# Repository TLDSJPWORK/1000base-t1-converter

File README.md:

# 1000base-t1-converter for Education

学習用 1000BASE-T1 Media Converter

## 特徴

- Texas Instruments社のDP83TG720とDP83867を使用した、1000BASE-T1 ↔ 1000BASE-T（RJ45）のメディアコンバーターです。
- RP2040を搭載し、USB接続で各PHY ICの状態確認とレジスタ設定ができます。MDIOを通してPHY層の動きを学習できます。
- 基板上のスイッチで1000BASE-T1のmaster／slaveを選択できます。
- Ethernetフレームは2個のPHY間をRGMIIで転送し、RP2040はPHYの設定・状態確認を担当します。
- KiCadの回路図・PCB、製造データ、ケースのSTL・STEPを公開しています。

## 基板

収録している回路・基板はRev1.0です。基板外形は125 × 70 mmです。
基板イメージは参考であり、改良により実物と異なる場合があります。

## 基板の設定と説明

| 図の番号 | 接続部 | 使い方 |
| --- | --- | --- |
| 1 | USB Type-C（USB601） | 5 V給電、USB診断、ファームウェア更新に使用します。 |
| 2 | Boot（SW601） | ファームウェア書込み時のBOOTSELボタンです。 |
| 3 | Reset（SW602） | RP2040と両PHY（DP83TG720・DP83867）をリセットします。master／slave変更後は全電源を再投入してください。 |
| 4 | Sleep / WAKE（U205） | 通常の通信ではWAKEをHighに設定します。接点状態は下表を参照してください。 |
| 5 | T1（CN201） | 1000BASE-T1を接続します。pin 1=T1_P、pin 2=T1_Nです。 |
| 6 | Master/Slave（U203） | 対向機器と、一方をmaster、もう一方をslaveに設定します。 |
| 7 | RJ45（RJ501） | 1000BASE-T対応機器を接続します。 |

### スイッチの接点設定

U203・U205はそれぞれ2回路のスイッチです。ONは接続、OFFは開放を示します。
図中の3Dモデルのレバー位置は設定例ではありません。スイッチ本体のON表示と端子番号を確認してください。

| スイッチ | 設定 | 1–4の接点 | 2–3の接点 |
| --- | --- | --- | --- |
| Master/Slave（U203） | **master** | **ON** | **OFF** |
| Master/Slave（U203） | **slave** | **OFF** | **ON** |
| Sleep / WAKE（U205） | **通常動作（WAKE=High）** | **ON** | **OFF** |
| Sleep / WAKE（U205） | Sleep要求（WAKE=Low） | **OFF** | **ON** |

**両回路を同時にONにしないでください。** 上表の組合せで、一方をON、もう一方をOFFにしてください。
Sleepへの移行はPHYの設定やリンク状態にも依存します。
設定変更は全電源を外して行い、変更後は基板の全電源を再投入してください。
詳しい接続手順と給電方法は[取扱説明書](docs/user-manual.md)を参照してください。

### LEDの説明

上の「基板の設定と説明」図の青い番号8〜14が、下表に対応します。14はRJ45内蔵の2個のLEDをまとめて示しています。

Power・Reset・RP_GPIO25は、基板手前のシルク表示で識別できます。
T1側にはSleepスイッチ付近のU202と、Master/Slaveスイッチ付近のU201・U204があります。

| 図の番号 | 表示・位置 | 部品 | 説明 |
| --- | --- | --- | --- |
| 8 | Power | D402（緑） | 基板の5 V電源に接続された給電表示です。 |
| 9 | Reset | LED602（赤） | RP2040と両PHY（DP83TG720・DP83867）の共通リセット表示です。共通リセット信号がLowの間に点灯し、Resetボタン操作時にも点灯します。 |
| 10 | RP_GPIO25 | LED601（緑） | RP2040のGPIO25で制御するLEDです。点灯・点滅の意味はファームウェアに依存します。 |
| 11 | T1側・Sleepスイッチ付近 | U202（緑） | DP83TG720のLED_1出力に接続しています。リンク成立で点灯し、送受信時に点滅します。 |
| 12 | T1側・Master/Slaveスイッチ付近 | U201（緑） | **Master設定時のリンク表示**です。DP83TG720のLED_0出力を表示します。 |
| 13 | T1側・Master/Slaveスイッチ付近 | U204（緑） | **Slave設定時のリンク表示**です。DP83TG720のLED_0出力を表示します。 |
| 14 | RJ45内蔵LED | RJ501・LED_0側 | DP83867のリンク表示です。 |
| 14 | RJ45内蔵LED | RJ501・LED_2側 | DP83867の送受信アクティビティ表示です。 |

PHY関連のLED表示は、レジスタ設定によって変更できます。
LED出力の仕様はTIの[DP83TG720R-Q1データシート（IO_MUX_CFG_1）](https://www.ti.com/lit/ds/symlink/dp83tg720r-q1.pdf)と
[DP83867IR/CRデータシート（LED Interface）](https://www.ti.com/lit/ds/symlink/dp83867ir.pdf)を参照してください。

## 使用例

### メディアコンバーターとして使う

RP2040に[専用ファームウェア](https://github.com/TLDSJPWORK/1000base-t1-converter-soft)を書き込み、
T1側のmaster／slaveを設定して、1000BASE-T1機器とRJ45側の1000BASE-T機器を接続します。
ファームウェアが起動時にPHYの通信設定を適用します。

2台を `Mac ↔ converter ↔ converter ↔ Raspberry Pi` と接続し、
1000BASE-T full-duplex、両T1 PHYのリンク、ARP、20回のping（損失0%）、SSHポート到達を確認しています。
詳しい試験条件と確認範囲は[検証記録](https://github.com/TLDSJPWORK/1000base-t1-converter-soft/blob/main/docs/validation.md)を参照してください。

### PHYの動きを確認する

USB CDCシリアルから、PHYの検出、リンク状態の確認、レジスタの読み書きができます。
コマンドと使用方法は[取扱説明書のUSB診断](docs/user-manual.md#4-usb診断)と
[ファームウェアのREADME](https://github.com/TLDSJPWORK/1000base-t1-converter-soft)を参照してください。

## ケースと完成品の構成

[PLAケース](case/)の設計外形は132.8 × 77.8 × 28.0 mmです。上下ケースのSTL・STEPを収録しています。

ケース組立例。手前にT1端子、設定スイッチ、RJ45端子が並びます。

ケース入り完成品には、MATEnetアダプタ（ツイストペア線接続・ケース付き）が付属します。アダプタの[基板設計・製造・ケースデータ](adapter/)も収録しています。

付属MATEnetアダプタの外観。本体側プラグの取付前の状態です。

## 製造データ

[Rev1.0の製造データ](production/)には、基板製作に使用したGerber ZIP・BOM・実装位置データを収録しています。
対応するKiCadソースは[hardware/](hardware/)に収録しています。

再製造する場合は、部品指定や未実装部品についての[Rev1.0の既知事項](docs/rev1.0-known-issues.md)を確認してください。

## 資料

- [取扱説明書](docs/user-manual.md)
- [回路図（PDF）](docs/1000base-t1-converter_schematic.pdf)
- [KiCad回路図・PCB](hardware/)
- [Gerber・BOM・実装位置](production/)
- [ケースのSTL・STEP](case/)
- [RP2040ファームウェア・レジスタ読み書きソフト](https://github.com/TLDSJPWORK/1000base-t1-converter-soft)
- [学習用100BASE-T1メディアコンバーター](https://github.com/TLDSJPWORK/100base-t1-converter)

## 販売・問い合わせ

スイッチサイエンス様での委託販売を予定しています。

- 販売ページ：【発売後掲載】
- 技術問い合わせ先：tldsjpwork@gmail.com

## 関連プロジェクト

- [100base-t1-converter](https://github.com/TLDSJPWORK/100base-t1-converter)：100 Mbpsの100BASE-T1に対応した学習用メディアコンバーターです。
- [1000base-t1-converter-soft](https://github.com/TLDSJPWORK/1000base-t1-converter-soft)：本基板のRP2040用ファームウェアです。PHYの初期設定、状態確認、レジスタの読み書きに使用します。

## ライセンス

ハードウェア設計、製造データ、文書、画像は[Creative Commons Attribution 4.0 International](LICENSE)で公開します。

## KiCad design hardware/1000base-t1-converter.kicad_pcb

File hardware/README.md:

# Hardware

KiCad 9で作成した1000BASE-T1コンバーター本体の設計データです。

`1000base-t1-converter.kicad_pro`を開いてください。回路図は次の階層シートに分かれています。

- `DP83867.kicad_sch`: 1000BASE-T PHY
- `DP83TG720.kicad_sch`: 1000BASE-T1 PHY
- `RJ45.kicad_sch`: RJ45インターフェース
- `RP2040.kicad_sch`: PHY管理マイコン
- `Power.kicad_sch`: 電源回路

製造データは[production/](../production/)にあります。

フットプリントと回路記号はKiCadファイルへ保存されています。3Dモデルの一部は
EasyEDA2KiCadのライブラリを参照するため、完全な3D表示にはKiCadで`EASYEDA2KICAD`
パス変数を設定してください。回路図・PCB編集と製造出力の確認には必須ではありません。

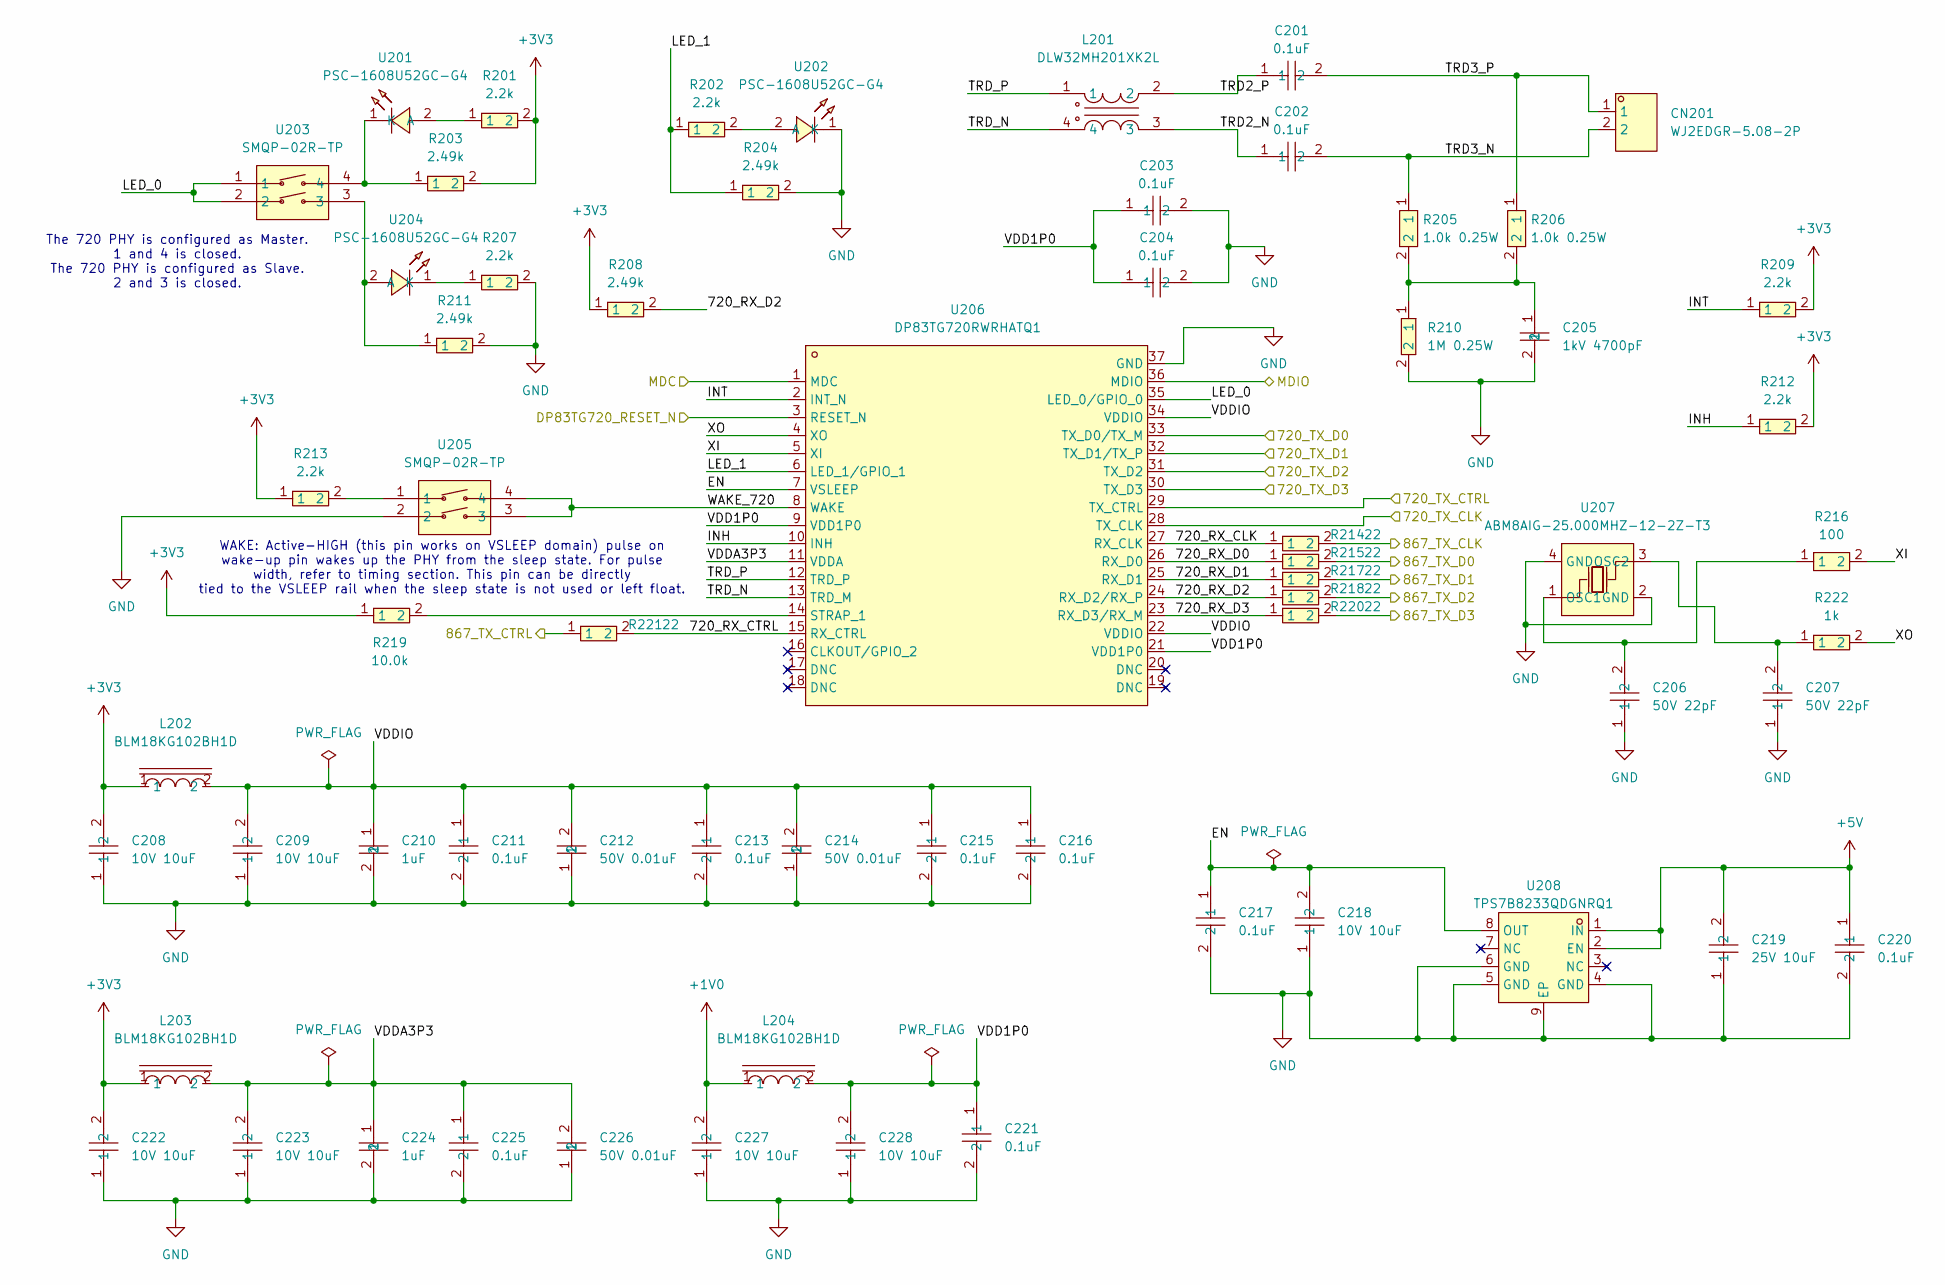
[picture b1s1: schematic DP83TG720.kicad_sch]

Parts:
C201, C202, C203, C204, C211, C213, C215, C216, C217, C220, C221, C225: 0.1uF; C0603; LCSC Part C14663
C205: 1kV 4700pF; C1206; LCSC Part C9192
C206, C207: 50V 22pF; C0603; LCSC Part C326840
C208, C209, C218, C222, C223, C227, C228: 10V 10uF; C0603; MPN GRM188Z71A106MA73D; LCSC Part C237435
C210, C224: 1uF; C0603; LCSC Part C15849
C212, C214, C226: 50V 0.01uF; C0603; LCSC Part C57112
C219: 25V 10uF; C0603; LCSC Part C96446
CN201: WJ2EDGR-5.08-2P; CONN-TH_WJ2EDGR-5.08-2P; MPN WJ2EDGR-5.08-02P-14-00A; LCSC Part C8383
L201: DLW32MH201XK2L; FILTER-SMD_4P-L3.2-W2.5-BL_DLW32SH510XK2L; MPN DLW32MH201XK2L; LCSC Part C883600
L202, L203, L204: BLM18KG102BH1D; L0603; MPN BLM18KG102BH1D; LCSC Part C560058
R201, R202, R207, R209, R212, R213: 2.2k; R0603; LCSC Part C4190
R203, R204, R208, R211: 2.49k; R0603; LCSC Part C22908
R205, R206: 1.0k 0.25W; R0603; LCSC Part C2653986
R210: 1M 0.25W; R1206; LCSC Part C108083
R214, R215, R217, R218, R220, R221: 22; R0603; LCSC Part C108405
R216: 100; R0603; LCSC Part C22775
R219: 10.0k; R0603; LCSC Part C25804
R222: 1k; R0603; LCSC Part C21190
U201, U202, U204: PSC-1608U52GC-G4; LED0603-RD_GREEN; LCSC Part C22371297
U203, U205: SMQP-02R-TP; SW-TH_4P-P2.54_SMQP-02R-TP; LCSC Part C5299482
U206: DP83TG720RWRHATQ1; UQFN-36_L6.0-W6.0-P0.50-BL-EP3.7; MPN DP83TG720RWRHATQ1; LCSC Part C2921292
U207: ABM8AIG-25.000MHZ-12-2Z-T3; CRYSTAL-SMD_4P-L3.2-W2.5-BL; MPN ABM8AIG-25.000MHZ-12-2Z-T3; LCSC Part C1985412
U208: TPS7B8233QDGNRQ1; HVSSOP-8_L3.0-W3.0-P0.65-LS4.9-BL-EP; MPN TPS7B8233QDGNRQ1; LCSC Part C5220182

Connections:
+1V0: C227.2, L204.1; also elsewhere on the board
+3V3: C208.2, C222.2, L202.1, L203.1, R201.2, R203.2, R208.1, R209.2, R212.2, R213.1, R219.1; also elsewhere on the board
+5V: C219.2, C220.1, U208.1 (IN), U208.2 (EN); also elsewhere on the board
/DP83TG720/720_RX_CLK: R214.1, U206.27 (RX_CLK)
/DP83TG720/720_RX_CTRL: R221.2, U206.15 (RX_CTRL)
/DP83TG720/720_RX_D0: R215.1, U206.26 (RX_D0)
/DP83TG720/720_RX_D1: R217.1, U206.25 (RX_D1)
/DP83TG720/720_RX_D2: R208.2, R218.1, U206.24 (RX_D2/RX_P)
/DP83TG720/720_RX_D3: R220.1, U206.23 (RX_D3/RX_M)
/DP83TG720/EN: C217.1, C218.2, U206.7 (VSLEEP), U208.8 (OUT)
/DP83TG720/INH: R212.1, U206.10 (INH)
/DP83TG720/INT: R209.1, U206.2 (INT_N)
/DP83TG720/LED_0: U203.1, U203.2, U206.35 (LED_0/GPIO_0)
/DP83TG720/LED_1: R202.1, R204.1, U206.6 (LED_1/GPIO_1)
/DP83TG720/TRD2_N: C202.1, L201.3
/DP83TG720/TRD2_P: C201.1, L201.2
/DP83TG720/TRD3_N: C202.2, CN201.2, R205.1
/DP83TG720/TRD3_P: C201.2, CN201.1, R206.1
/DP83TG720/TRD_N: L201.4, U206.13 (TRD_M)
/DP83TG720/TRD_P: L201.1, U206.12 (TRD_P)
/DP83TG720/VDD1P0: C203.1, C204.1, C221.1, C228.2, L204.2, U206.9 (VDD1P0), U206.21 (VDD1P0)
/DP83TG720/VDDA3P3: C223.2, C224.1, C225.1, C226.2, L203.2, U206.11 (VDDA)
/DP83TG720/VDDIO: C209.2, C210.1, C211.1, C212.2, C213.1, C214.2, C215.1, C216.1, L202.2, U206.22 (VDDIO), U206.34 (VDDIO)
/DP83TG720/WAKE_720: U205.3, U205.4, U206.8 (WAKE)
/DP83TG720/XI: R216.2, U206.5 (XI)
/DP83TG720/XO: R222.2, U206.4 (XO)
/DP83867/720_TX_CLK: U206.28 (TX_CLK); also elsewhere on the board
/DP83867/720_TX_CTRL: U206.29 (TX_CTRL); also elsewhere on the board
/DP83867/720_TX_D0: U206.33 (TX_D0/TX_M); also elsewhere on the board
/DP83867/720_TX_D1: U206.32 (TX_D1/TX_P); also elsewhere on the board
/DP83867/720_TX_D2: U206.31 (TX_D2); also elsewhere on the board
/DP83867/720_TX_D3: U206.30 (TX_D3); also elsewhere on the board
/DP83867/867_TX_CLK: R214.2; also elsewhere on the board
/DP83867/867_TX_CTRL: R221.1; also elsewhere on the board
/DP83867/867_TX_D0: R215.2; also elsewhere on the board
/DP83867/867_TX_D1: R217.2; also elsewhere on the board
/DP83867/867_TX_D2: R218.2; also elsewhere on the board
/DP83867/867_TX_D3: R220.2; also elsewhere on the board
/DP83867/83867_RESET_N: U206.3 (RESET_N); also elsewhere on the board
/DP83867/MDC: U206.1 (MDC); also elsewhere on the board
/DP83867/MDIO: U206.36 (MDIO); also elsewhere on the board
GND: C203.2, C204.2, C205.2, C206.1, C207.1, C208.1, C209.1, C210.2, C211.2, C212.1, C213.2, C214.1, C215.2, C216.2, C217.2, C218.1, C219.1, C220.2, C221.2, C222.1, C223.1, C224.2, C225.2, C226.1, C227.1, C228.1, R204.2, R207.2, R210.2, R211.2, U202.1 (K), U205.2, U206.37 (GND), U207.2 (GND), U207.4 (GND), U208.4 (GND), U208.5 (GND), U208.6 (GND), U208.9 (EP); also elsewhere on the board
unnamed: C205.1, R205.2, R206.2, R210.1
unnamed: R213.2, U205.1
unnamed: R201.1, U201.2 (A)
unnamed: R203.1, U201.1 (K), U203.4
unnamed: R202.2, U202.2 (A)
unnamed: R211.1, U203.3, U204.2 (A)
unnamed: R207.1, U204.1 (K)
unnamed: R219.2, U206.14 (STRAP_1)
unnamed: C206.2, R216.1, U207.1 (OSC1)
unnamed: C207.2, R222.1, U207.3 (OSC2)

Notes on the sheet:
The 720 PHY is configured as Master. 1 and 4 is closed. The 720 PHY is configured as Slave. 2 and 3 is closed.
WAKE: Active-HIGH (this pin works on VSLEEP domain) pulse on wake-up pin wakes up the PHY from the sleep state. For pulse width, refer to timing section. This pin can be directly tied to the VSLEEP rail when the sleep state is not used or left float.

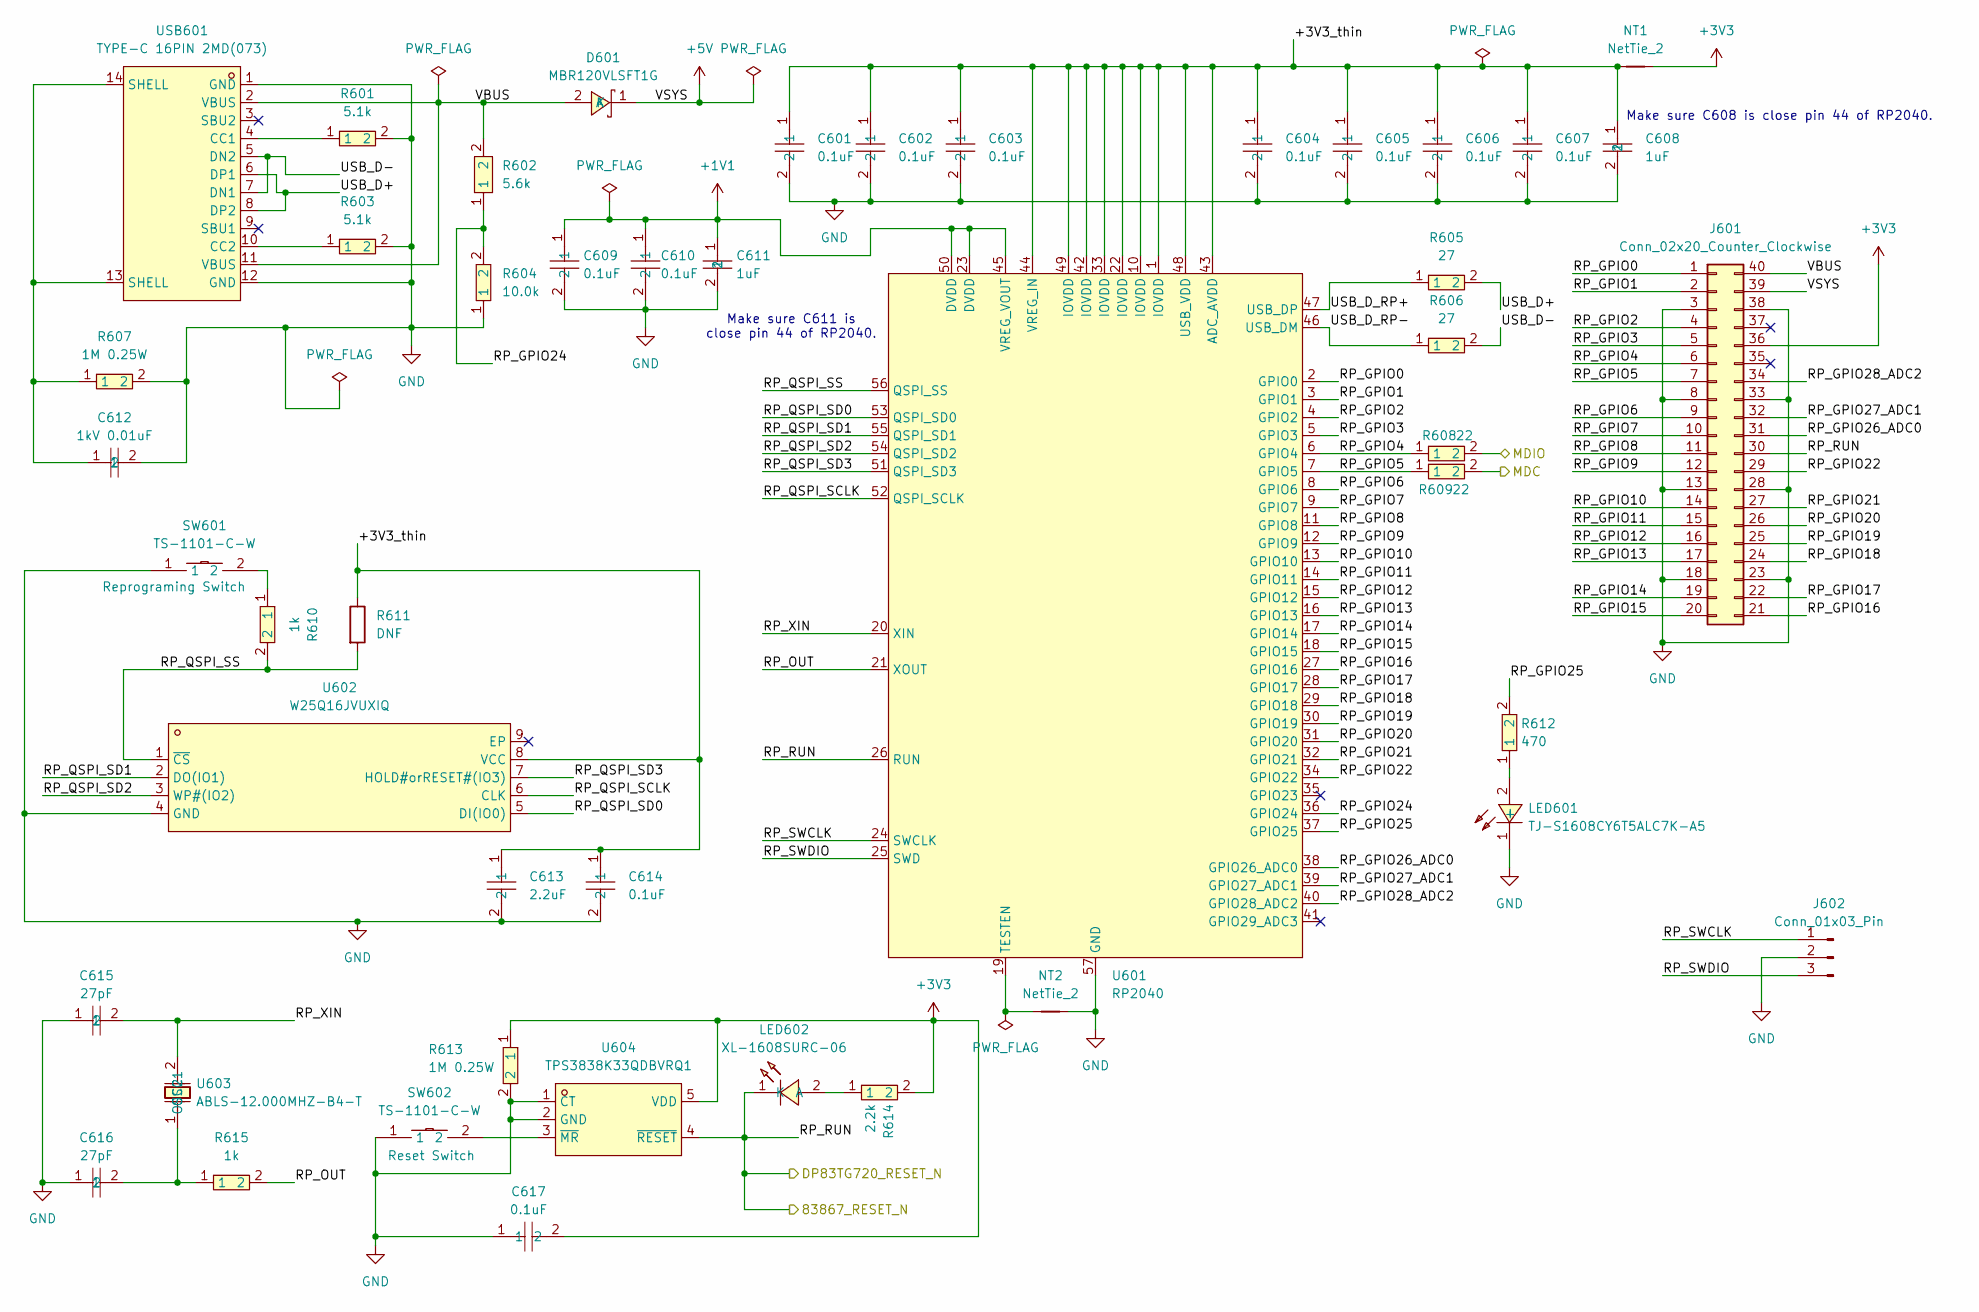
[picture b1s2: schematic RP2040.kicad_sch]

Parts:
C601, C602, C603, C604, C605, C606, C607, C609, C610, C614, C617: 0.1uF; C0603; LCSC Part C14663
C608, C611: 1uF; C0603; LCSC Part C15849
C612: 1kV 0.01uF; C1206; LCSC Part C107192
C613: 2.2uF; C0603; LCSC Part C307463
C615, C616: 27pF; C0603; LCSC Part C107045
D601: MBR120VLSFT1G; SOD-123F_L2.8-W1.8-LS3.7-RD; LCSC Part C223608
J601: Conn_02x20_Counter_Clockwise; PinSocket_2x20_P2.54mm_Vertical
J602: Conn_01x03_Pin; PinHeader_1x03_P2.54mm_Vertical
LED601: TJ-S1608CY6T5ALC7K-A5; LED0603-RD_GREEN; LCSC Part C440520
LED602: XL-1608SURC-06; LED0603-RD_RED; LCSC Part C965799
NT1, NT2: NetTie_2; NetTie-2_SMD_Pad0.5mm
R601, R603: 5.1k; R1206; LCSC Part C163372
R602: 5.6k; R0603; LCSC Part C23189
R604: 10.0k; R0603; LCSC Part C25804
R605, R606: 27; R0603; LCSC Part C137753
R607, R613: 1M 0.25W; R1206; LCSC Part C108083
R608, R609: 22; R0603; LCSC Part C108405
R610, R615: 1k; R0603; LCSC Part C21190
R611: DNF; R0603
R612: 470; R0603; LCSC Part C23179
R614: 2.2k; R0603; LCSC Part C4190
SW601, SW602: TS-1101-C-W; SW-SMD_L6.0-W3.3-LS8.0; LCSC Part C318938
U601: RP2040; LQFN-56_L7.0-W7.0-P0.4-EP; LCSC Part C2040
U602: W25Q16JVUXIQ; USON-8_L3.0-W2.0-P0.50-BL-EP; LCSC Part C2843335
U603: ABLS-12.000MHZ-B4-T; CRYSTAL-SMD_L11.5-W4.8-LS12.7; LCSC Part C596818
U604: TPS3838K33QDBVRQ1; SOT-23-5_L2.9-W1.6-P0.95-LS2.8-BR; LCSC Part C702198
USB601: TYPE-C 16PIN 2MD(073); USB-C-SMD_TYPE-C-6PIN-2MD-073; LCSC Part C2765186

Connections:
+1V1: C609.1, C610.1, C611.1, U601.23 (DVDD), U601.45 (VREG_VOUT), U601.50 (DVDD)
+3V3: C617.2, J601.36, NT1.2, R613.1, R614.2, U604.5 (VDD); also elsewhere on the board
+5V: D601.1 (K), J601.39; also elsewhere on the board
/DP83867/83867_RESET_N: J601.30, LED602.1 (K), U601.26 (RUN), U604.4 (~RESET); also elsewhere on the board
/DP83867/MDC: R609.2; also elsewhere on the board
/DP83867/MDIO: R608.2; also elsewhere on the board
/RP2040/+3V3_thin: C601.1, C602.1, C603.1, C604.1, C605.1, C606.1, C607.1, C608.1, C613.1, C614.1, NT1.1, R611.1, U601.1 (IOVDD), U601.10 (IOVDD), U601.22 (IOVDD), U601.33 (IOVDD), U601.42 (IOVDD), U601.43 (ADC_AVDD), U601.44 (VREG_IN), U601.48 (USB_VDD), U601.49 (IOVDD), U602.8 (VCC)
/RP2040/RP_GPIO0: J601.1, U601.2 (GPIO0)
/RP2040/RP_GPIO1: J601.2, U601.3 (GPIO1)
/RP2040/RP_GPIO2: J601.4, U601.4 (GPIO2)
/RP2040/RP_GPIO3: J601.5, U601.5 (GPIO3)
/RP2040/RP_GPIO4: J601.6, R608.1, U601.6 (GPIO4)
/RP2040/RP_GPIO5: J601.7, R609.1, U601.7 (GPIO5)
/RP2040/RP_GPIO6: J601.9, U601.8 (GPIO6)
/RP2040/RP_GPIO7: J601.10, U601.9 (GPIO7)
/RP2040/RP_GPIO8: J601.11, U601.11 (GPIO8)
/RP2040/RP_GPIO9: J601.12, U601.12 (GPIO9)
/RP2040/RP_GPIO10: J601.14, U601.13 (GPIO10)
/RP2040/RP_GPIO11: J601.15, U601.14 (GPIO11)
/RP2040/RP_GPIO12: J601.16, U601.15 (GPIO12)
/RP2040/RP_GPIO13: J601.17, U601.16 (GPIO13)
/RP2040/RP_GPIO14: J601.19, U601.17 (GPIO14)
/RP2040/RP_GPIO15: J601.20, U601.18 (GPIO15)
/RP2040/RP_GPIO16: J601.21, U601.27 (GPIO16)
/RP2040/RP_GPIO17: J601.22, U601.28 (GPIO17)
/RP2040/RP_GPIO18: J601.24, U601.29 (GPIO18)
/RP2040/RP_GPIO19: J601.25, U601.30 (GPIO19)
/RP2040/RP_GPIO20: J601.26, U601.31 (GPIO20)
/RP2040/RP_GPIO21: J601.27, U601.32 (GPIO21)
/RP2040/RP_GPIO22: J601.29, U601.34 (GPIO22)
/RP2040/RP_GPIO24: R602.1, R604.2, U601.36 (GPIO24)
/RP2040/RP_GPIO25: R612.2, U601.37 (GPIO25)
/RP2040/RP_GPIO26_ADC0: J601.31, U601.38 (GPIO26_ADC0)
/RP2040/RP_GPIO27_ADC1: J601.32, U601.39 (GPIO27_ADC1)
/RP2040/RP_GPIO28_ADC2: J601.34, U601.40 (GPIO28_ADC2)
/RP2040/RP_OUT: R615.2, U601.21 (XOUT)
/RP2040/RP_QSPI_SCLK: U601.52 (QSPI_SCLK), U602.6 (CLK)
/RP2040/RP_QSPI_SD0: U601.53 (QSPI_SD0), U602.5 (DI(IO0))
/RP2040/RP_QSPI_SD1: U601.55 (QSPI_SD1), U602.2 (DO(IO1))
/RP2040/RP_QSPI_SD2: U601.54 (QSPI_SD2), U602.3 (WP#(IO2))
/RP2040/RP_QSPI_SD3: U601.51 (QSPI_SD3), U602.7 (HOLD#orRESET#(IO3))
/RP2040/RP_QSPI_SS: R610.2, R611.2, U601.56 (QSPI_SS), U602.1 (~CS)
/RP2040/RP_SWCLK: J602.1, U601.24 (SWCLK)
/RP2040/RP_SWDIO: J602.3, U601.25 (SWD)
/RP2040/RP_XIN: C615.2, U601.20 (XIN), U603.2 (OSC2)
/RP2040/USB_D+: R605.2, USB601.6 (DP1), USB601.8 (DP2)
/RP2040/USB_D-: R606.2, USB601.5 (DN2), USB601.7 (DN1)
/RP2040/USB_D_RP+: R605.1, U601.47 (USB_DP)
/RP2040/USB_D_RP-: R606.1, U601.46 (USB_DM)
/RP2040/VBUS: D601.2 (A), J601.40, R602.2, USB601.2 (VBUS), USB601.11 (VBUS)
GND: C601.2, C602.2, C603.2, C604.2, C605.2, C606.2, C607.2, C608.2, C609.2, C610.2, C611.2, C612.2, C613.2, C614.2, C615.1, C616.1, C617.1, J601.3, J601.8, J601.13, J601.18, J601.23, J601.28, J601.33, J601.38, J602.2, LED601.1 (-), NT2.2, R601.2, R603.2, R604.1, R607.2, R613.2, SW601.1, SW602.1, U601.57 (GND), U602.4 (GND), U604.1 (CT), U604.2 (GND), USB601.1 (GND), USB601.12 (GND); also elsewhere on the board
unnamed: C612.1, R607.1, USB601.13 (SHELL), USB601.14 (SHELL)
unnamed: LED601.2 (+), R612.1
unnamed: LED602.2 (A), R614.1
unnamed: R610.1, SW601.2
unnamed: NT2.1, U601.19 (TESTEN)
unnamed: C616.2, R615.1, U603.1 (OSC1)
unnamed: SW602.2, U604.3 (~MR)
unnamed: R601.1, USB601.4 (CC1)
unnamed: R603.1, USB601.10 (CC2)

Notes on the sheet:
Make sure C608 is close pin 44 of RP2040.
Make sure C611 is close pin 44 of RP2040.

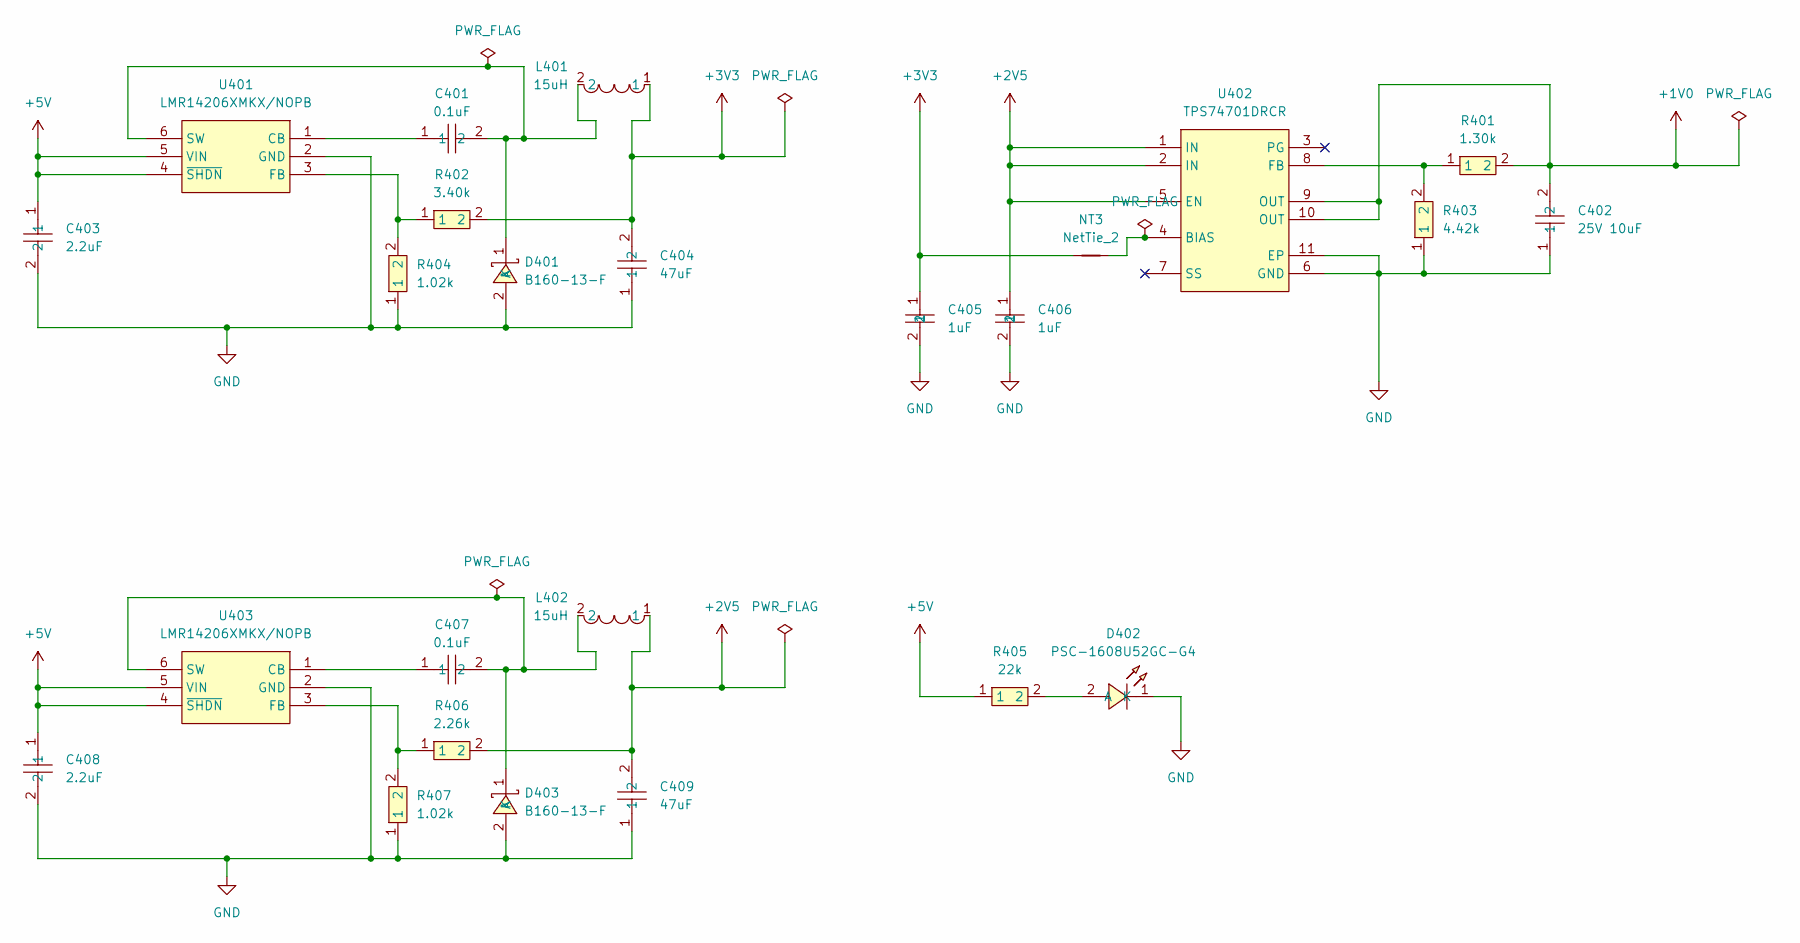
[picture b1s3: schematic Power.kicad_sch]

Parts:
C401, C407: 0.1uF; C0603; LCSC Part C14663
C402: 25V 10uF; C0603; LCSC Part C96446
C403, C408: 2.2uF; C0603; LCSC Part C307463
C404, C409: 47uF; C0805; LCSC Part C124129
C405, C406: 1uF; C0603; LCSC Part C15849
D401, D403: B160-13-F; SMA_L4.3-W2.6-LS5.2-RD; LCSC Part C24784
D402: PSC-1608U52GC-G4; LED0603-RD_GREEN; LCSC Part C22371297
L401, L402: 15uH; IND-SMD_L7.1-W6.6; LCSC Part C149585
NT3: NetTie_2; NetTie-2_SMD_Pad0.5mm
R401: 1.30k; R0603; LCSC Part C705951
R402: 3.40k; R0603; LCSC Part C705984
R403: 4.42k; R0603; LCSC Part C728617
R404, R407: 1.02k; R0603; LCSC Part C705819
R405: 22k; R0603; LCSC Part C31850
R406: 2.26k; R0603; LCSC Part C861811
U401, U403: LMR14206XMKX/NOPB; SOT-23-6_L2.9-W1.6-P0.95-LS2.8-BR; LCSC Part C48239
U402: TPS74701DRCR; VSON-10_L3.0-W3.0-P0.50-TL-EP; MPN TPS74701DRCR; LCSC Part C105262

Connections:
+1V0: C402.2, R401.2, U402.9 (OUT), U402.10 (OUT); also elsewhere on the board
+2V5: C406.1, C409.2, L402.1, R406.2, U402.1 (IN), U402.2 (IN), U402.5 (EN); also elsewhere on the board
+3V3: C404.2, C405.1, L401.1, NT3.1, R402.2; also elsewhere on the board
+5V: C403.1, C408.1, R405.1, U401.4 (~SHDN), U401.5 (VIN), U403.4 (~SHDN), U403.5 (VIN); also elsewhere on the board
GND: C402.1, C403.2, C404.1, C405.2, C406.2, C408.2, C409.1, D401.2 (A), D402.1 (K), D403.2 (A), R403.1, R404.1, R407.1, U401.2 (GND), U402.6 (GND), U402.11 (EP), U403.2 (GND); also elsewhere on the board
unnamed: C401.2, D401.1 (K), L401.2, U401.6 (SW)
unnamed: D402.2 (A), R405.2
unnamed: C407.2, D403.1 (K), L402.2, U403.6 (SW)
unnamed: C401.1, U401.1 (CB)
unnamed: R402.1, R404.2, U401.3 (FB)
unnamed: NT3.2, U402.4 (BIAS)
unnamed: R401.1, R403.2, U402.8 (FB)
unnamed: C407.1, U403.1 (CB)
unnamed: R406.1, R407.2, U403.3 (FB)

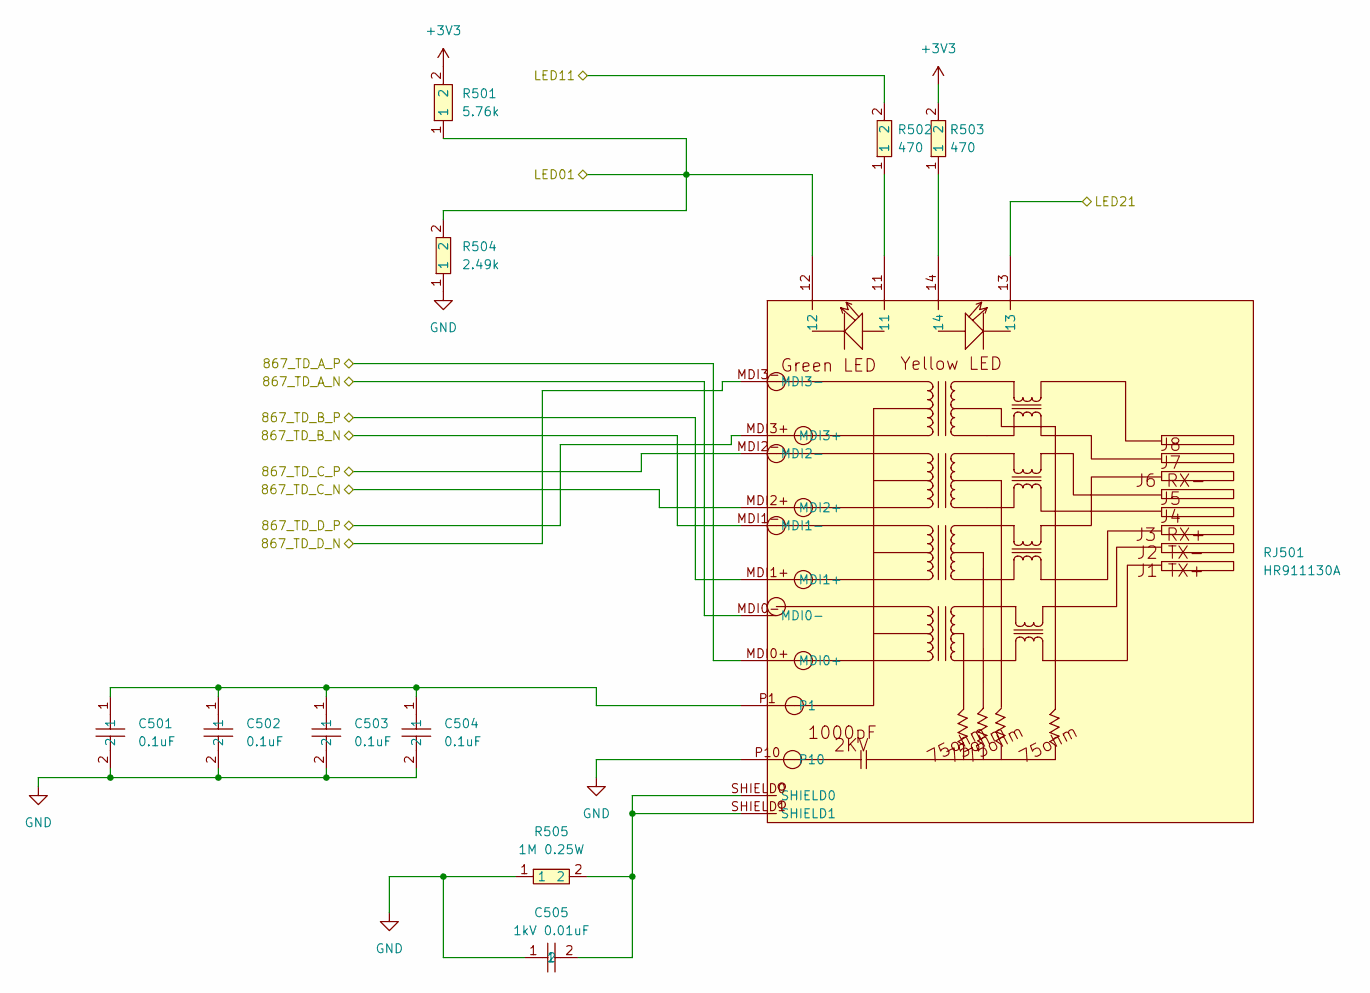
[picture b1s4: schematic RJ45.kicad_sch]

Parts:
C501, C502, C503, C504: 0.1uF; C0603; LCSC Part C14663
C505: 1kV 0.01uF; C1206; LCSC Part C107192
R501: 5.76k; R0603; LCSC Part C23070
R502, R503: 470; R0603; LCSC Part C23179
R504: 2.49k; R0603; LCSC Part C22908
R505: 1M 0.25W; R1206; LCSC Part C108083
RJ501: HR911130A; RJ45-TH_HR911130A; MPN HR911130A; LCSC Part C54408

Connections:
+3V3: R501.2, R503.2; also elsewhere on the board
/DP83867/867_TD_A_N: RJ501.MDI0-; also elsewhere on the board
/DP83867/867_TD_A_P: RJ501.MDI0+; also elsewhere on the board
/DP83867/867_TD_B_N: RJ501.MDI1-; also elsewhere on the board
/DP83867/867_TD_B_P: RJ501.MDI1+; also elsewhere on the board
/DP83867/867_TD_C_N: RJ501.MDI2+; also elsewhere on the board
/DP83867/867_TD_C_P: RJ501.MDI2-; also elsewhere on the board
/DP83867/867_TD_D_N: RJ501.MDI3-; also elsewhere on the board
/DP83867/867_TD_D_P: RJ501.MDI3+; also elsewhere on the board
/DP83867/LED01: R501.1, R504.2, RJ501.12; also elsewhere on the board
/DP83867/LED11: R502.2; also elsewhere on the board
/DP83867/LED21: RJ501.13; also elsewhere on the board
GND: C501.2, C502.2, C503.2, C504.2, C505.1, R504.1, R505.1, RJ501.P10; also elsewhere on the board
unnamed: C501.1, C502.1, C503.1, C504.1, RJ501.P1
unnamed: C505.2, R505.2, RJ501.SHIELD0, RJ501.SHIELD1
unnamed: R502.1, RJ501.11
unnamed: R503.1, RJ501.14

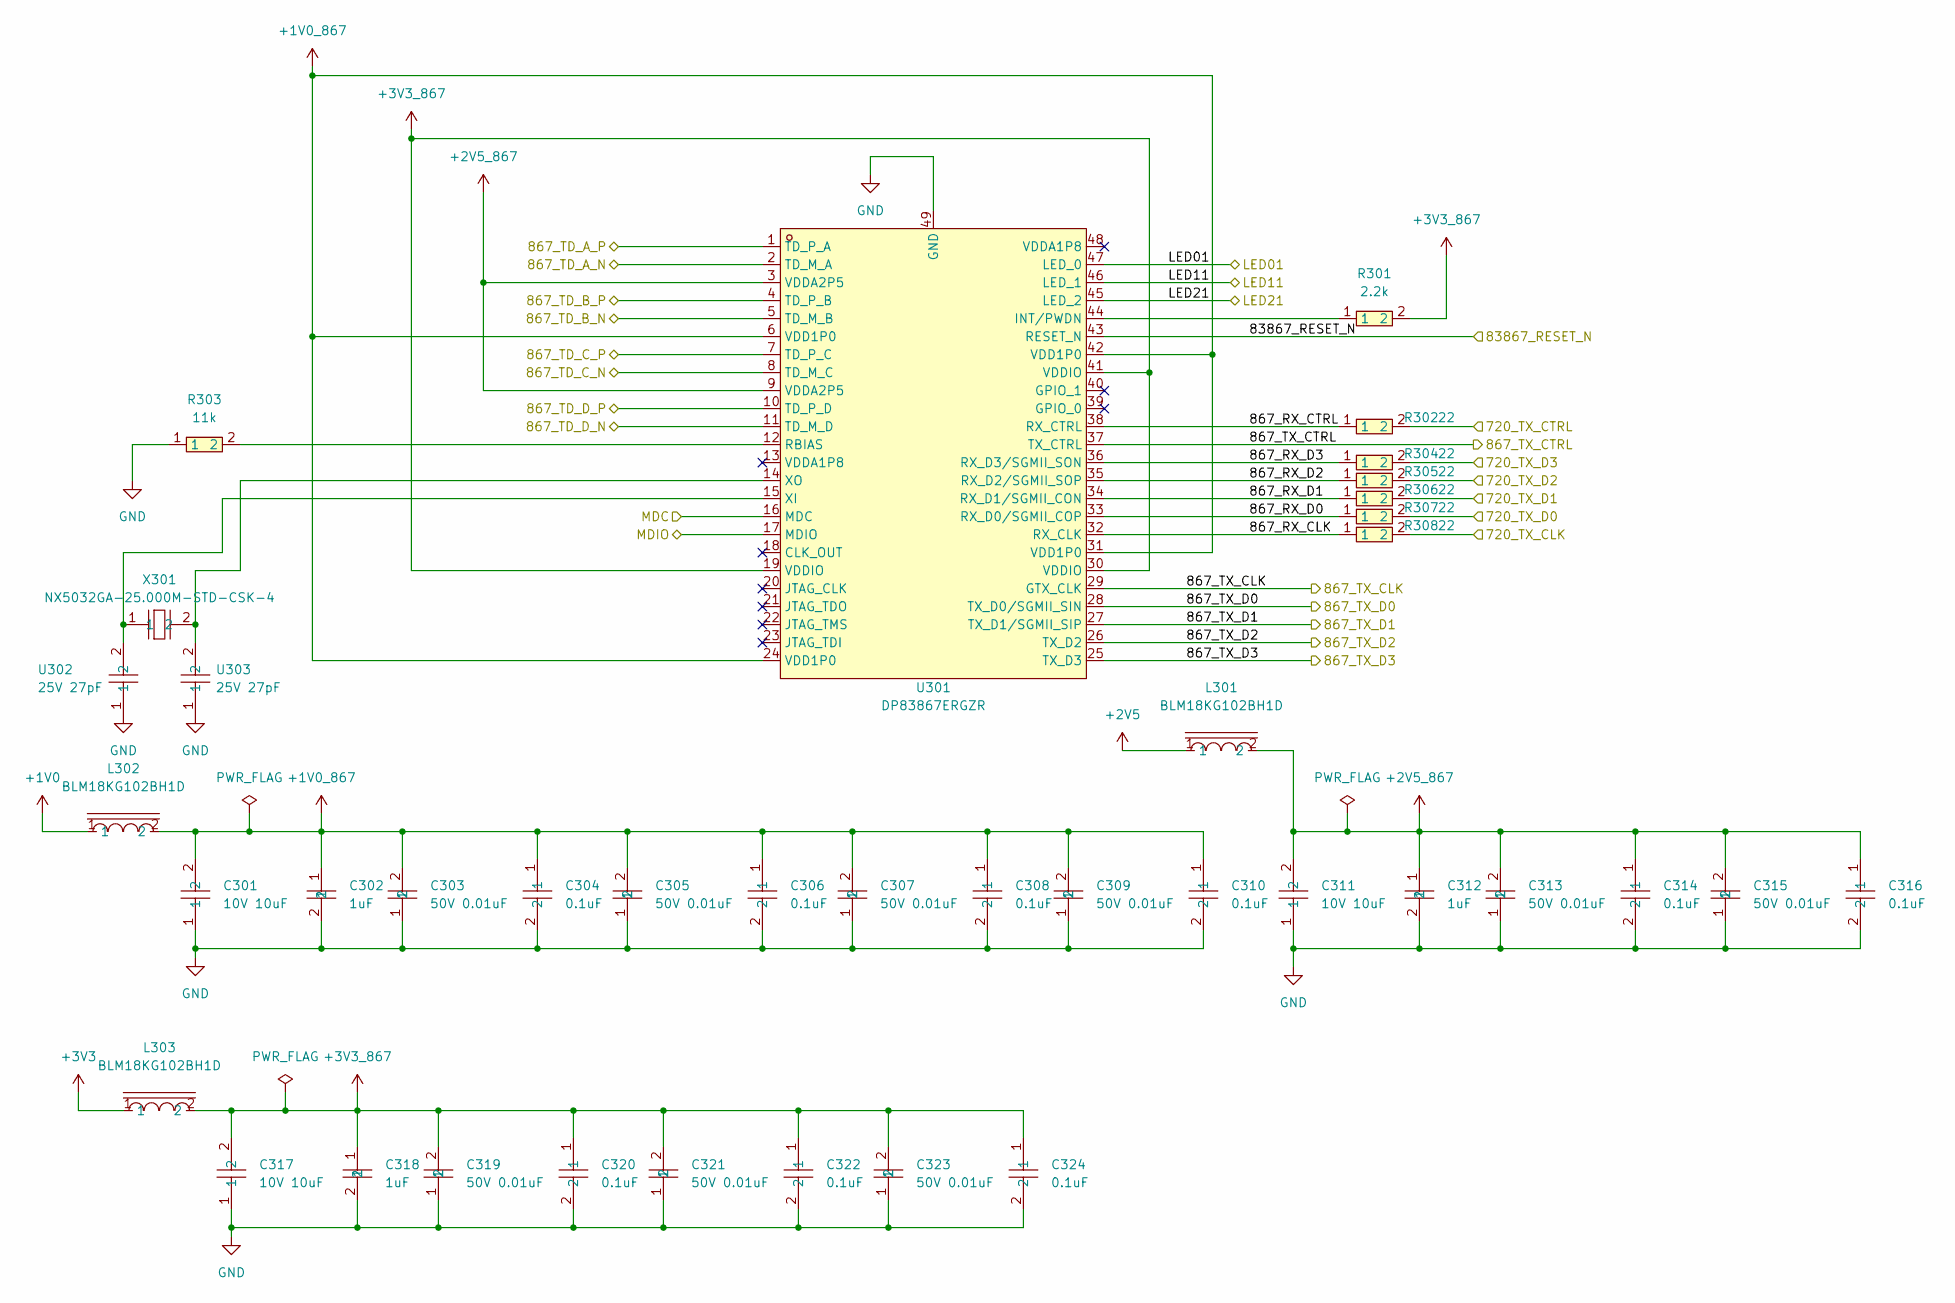
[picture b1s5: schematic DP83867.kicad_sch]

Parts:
C301, C311, C317: 10V 10uF; C0603; MPN GRM188Z71A106MA73D; LCSC Part C237435
C302, C312, C318: 1uF; C0603; LCSC Part C15849
C303, C305, C307, C309, C313, C315, C319, C321, C323: 50V 0.01uF; C0603; LCSC Part C57112
C304, C306, C308, C310, C314, C316, C320, C322, C324: 0.1uF; C0603; LCSC Part C14663
L301, L302, L303: BLM18KG102BH1D; L0603; MPN BLM18KG102BH1D; LCSC Part C560058
R301: 2.2k; R0603; LCSC Part C4190
R302, R304, R305, R306, R307, R308: 22; R0603; LCSC Part C108405
R303: 11k; R0603; LCSC Part C137801
U301: DP83867ERGZR; VQFN-48_L7.0-W7.0-P0.50-BL-EP4.1; MPN DP83867ERGZR; LCSC Part C913839
U302, U303: 25V 27pF; C0603; LCSC Part C1656
X301: NX5032GA-25.000M-STD-CSK-4; OSC-SMD_L5.0-W3.2; MPN NX5032GA-25.000M-STD-CSK-4; LCSC Part C115092

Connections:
+1V0: L302.1; also elsewhere on the board
+1V0_867: C301.2, C302.1, C303.2, C304.1, C305.2, C306.1, C307.2, C308.1, C309.2, C310.1, L302.2, U301.6 (VDD1P0), U301.24 (VDD1P0), U301.31 (VDD1P0), U301.42 (VDD1P0)
+2V5: L301.1; also elsewhere on the board
+2V5_867: C311.2, C312.1, C313.2, C314.1, C315.2, C316.1, L301.2, U301.3 (VDDA2P5), U301.9 (VDDA2P5)
+3V3: L303.1; also elsewhere on the board
+3V3_867: C317.2, C318.1, C319.2, C320.1, C321.2, C322.1, C323.2, C324.1, L303.2, R301.2, U301.19 (VDDIO), U301.30 (VDDIO), U301.41 (VDDIO)
/DP83867/720_TX_CLK: R308.2; also elsewhere on the board
/DP83867/720_TX_CTRL: R302.2; also elsewhere on the board
/DP83867/720_TX_D0: R307.2; also elsewhere on the board
/DP83867/720_TX_D1: R306.2; also elsewhere on the board
/DP83867/720_TX_D2: R305.2; also elsewhere on the board
/DP83867/720_TX_D3: R304.2; also elsewhere on the board
/DP83867/867_RX_CLK: R308.1, U301.32 (RX_CLK)
/DP83867/867_RX_CTRL: R302.1, U301.38 (RX_CTRL)
/DP83867/867_RX_D0: R307.1, U301.33 (RX_D0/SGMII_COP)
/DP83867/867_RX_D1: R306.1, U301.34 (RX_D1/SGMII_CON)
/DP83867/867_RX_D2: R305.1, U301.35 (RX_D2/SGMII_SOP)
/DP83867/867_RX_D3: R304.1, U301.36 (RX_D3/SGMII_SON)
/DP83867/867_TD_A_N: U301.2 (TD_M_A); also elsewhere on the board
/DP83867/867_TD_A_P: U301.1 (TD_P_A); also elsewhere on the board
/DP83867/867_TD_B_N: U301.5 (TD_M_B); also elsewhere on the board
/DP83867/867_TD_B_P: U301.4 (TD_P_B); also elsewhere on the board
/DP83867/867_TD_C_N: U301.8 (TD_M_C); also elsewhere on the board
/DP83867/867_TD_C_P: U301.7 (TD_P_C); also elsewhere on the board
/DP83867/867_TD_D_N: U301.11 (TD_M_D); also elsewhere on the board
/DP83867/867_TD_D_P: U301.10 (TD_P_D); also elsewhere on the board
/DP83867/867_TX_CLK: U301.29 (GTX_CLK); also elsewhere on the board
/DP83867/867_TX_CTRL: U301.37 (TX_CTRL); also elsewhere on the board
/DP83867/867_TX_D0: U301.28 (TX_D0/SGMII_SIN); also elsewhere on the board
/DP83867/867_TX_D1: U301.27 (TX_D1/SGMII_SIP); also elsewhere on the board
/DP83867/867_TX_D2: U301.26 (TX_D2); also elsewhere on the board
/DP83867/867_TX_D3: U301.25 (TX_D3); also elsewhere on the board
/DP83867/83867_RESET_N: U301.43 (RESET_N); also elsewhere on the board
/DP83867/LED01: U301.47 (LED_0); also elsewhere on the board
/DP83867/LED11: U301.46 (LED_1); also elsewhere on the board
/DP83867/LED21: U301.45 (LED_2); also elsewhere on the board
/DP83867/MDC: U301.16 (MDC); also elsewhere on the board
/DP83867/MDIO: U301.17 (MDIO); also elsewhere on the board
GND: C301.1, C302.2, C303.1, C304.2, C305.1, C306.2, C307.1, C308.2, C309.1, C310.2, C311.1, C312.2, C313.1, C314.2, C315.1, C316.2, C317.1, C318.2, C319.1, C320.2, C321.1, C322.2, C323.1, C324.2, R303.1, U301.49 (GND), U302.1, U303.1; also elsewhere on the board
unnamed: R301.1, U301.44 (INT/PWDN)
unnamed: R303.2, U301.12 (RBIAS)
unnamed: U301.15 (XI), U302.2, X301.1
unnamed: U301.14 (XO), U303.2, X301.2
